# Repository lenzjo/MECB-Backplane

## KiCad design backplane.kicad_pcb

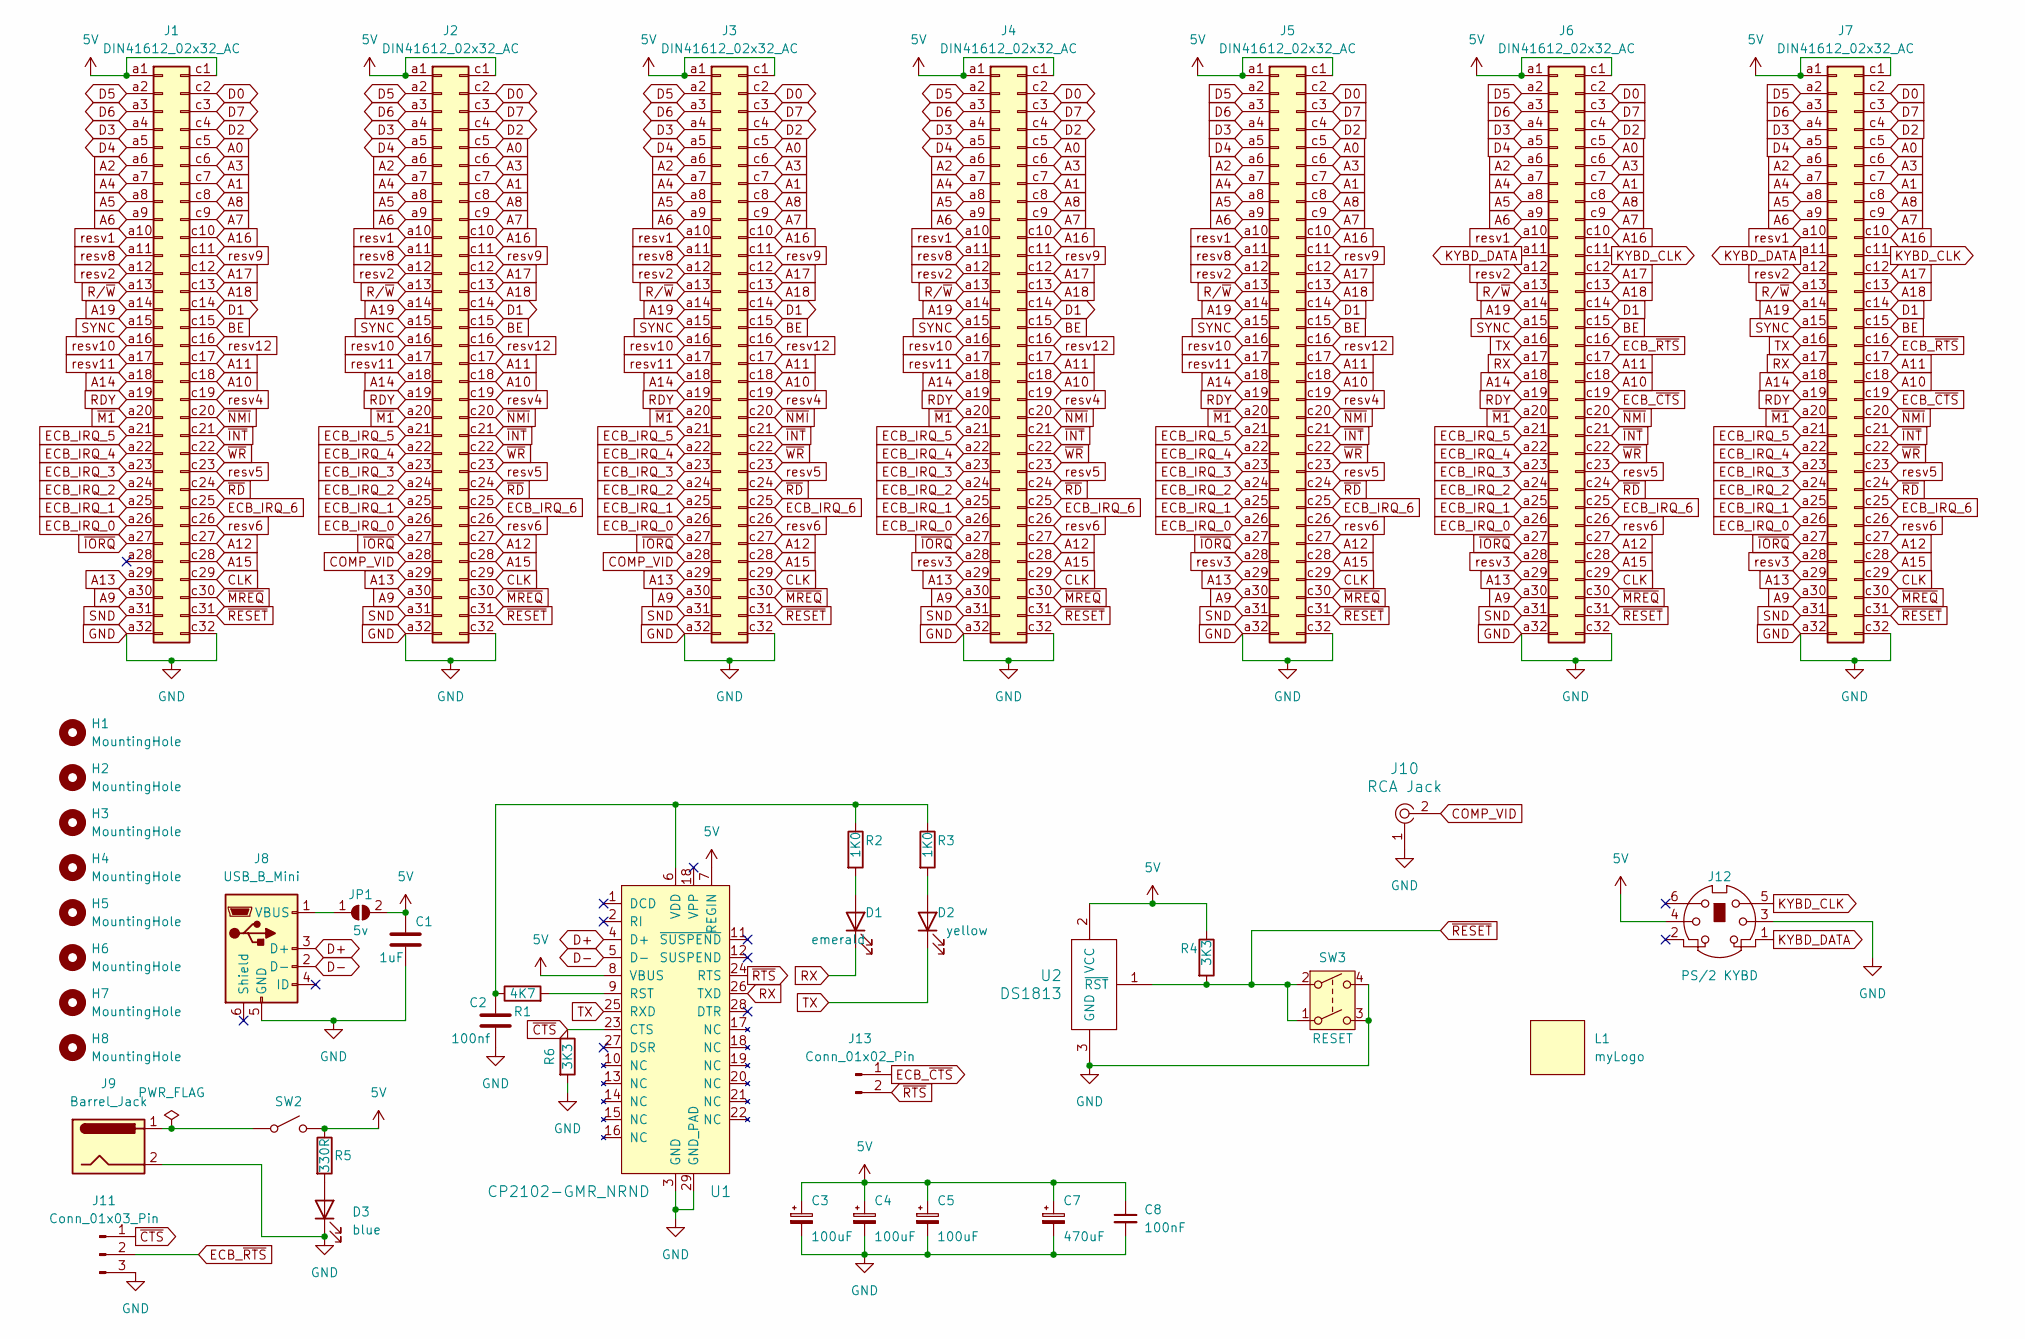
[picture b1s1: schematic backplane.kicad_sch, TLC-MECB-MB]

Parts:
C1: 1uF; C_0805_2012Metric; LCSC Part Number C28323
C2: 100nf; C_0805_2012Metric; LCSC Part Number C49678
C3, C4, C5: 100uF; CP_Radial_D6.3mm_P2.50mm
C7: 470uF; CP_Radial_D6.3mm_P2.50mm
C8: 100nF; C_Disc_D5.0mm_W2.5mm_P5.00mm
D1: emerald; LED_0603_1608Metric; LCSC Part Number C131259
D2: yellow; LED_0603_1608Metric; LCSC Part Number C264446
D3: blue; LED_1206_3216Metric; LCSC Part Number C131214
H1, H2, H3, H4, H5, H6, H7, H8: MountingHole; MountingHole_3.2mm_M3_DIN965
J1: DIN41612_02x32_AC; DIN41612_R_2x32_Female_Horizontal_THT
J2, J3, J4, J5, J6, J7: DIN41612_02x32_AC; DIN41612_C_2x32_Female_Vertical_THT
J8: USB_B_Mini; USB_Mini-B_5Pin
J9: Barrel_Jack; BarrelJack_GCT_DCJ200-10-A_Horizontal
J10: RCA Jack; RCA Video Jack; MPN 5-1814832-1; Digi-Key_PN A97594-ND
J11: Conn_01x03_Pin; PinHeader_1x03_P2.54mm_Vertical
J12: PS/2 KYBD; MINI-DIN-6-FULL-SHIELD
J13: Conn_01x02_Pin; PinHeader_1x02_P2.54mm_Vertical
JP1: 5v; SolderJumper-2_P1.3mm_Open_RoundedPad1.0x1.5mm
L1: myLogo; LOGO_sm
R1: 4K7; R_0805_2012Metric; LCSC Part Number C17673
R2, R3: 1K0; R_0805_2012Metric; LCSC Part Number C17513
R4, R6: 3K3; R_0805_2012Metric; LCSC Part Number C3016695
R5: 330R; R_0402_1005Metric; LCSC Part Number C156103
SW2: PTH_RA_h7.5mm; SPST Switch Mini
SW3: RESET; 12x12-Tactile-Switch
U1: CP2102-GMR_NRND; QFN-28-1EP_5x5mm_P0.5mm_EP3.35x3.35mm; MPN CP2102-GMR; Digi-Key_PN 336-1160-1-ND
U2: DS1813; 21-0248A_MXM

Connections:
5V: C1.1, C3.1, C4.1, C5.1, C7.1, C8.1, J1.a1, J1.c1, J2.a1, J2.c1, J3.a1, J3.c1, J4.a1, J4.c1, J5.a1, J5.c1, J6.a1, J6.c1, J7.a1, J7.c1, J12.4, JP1.2 (B), R4.1, R5.1, SW2.2 (B), U1.7 (REGIN), U1.8 (VBUS), U2.2 (VCC)
A0: J1.c5, J2.c5, J3.c5, J4.c5, J5.c5, J6.c5, J7.c5
A1: J1.c7, J2.c7, J3.c7, J4.c7, J5.c7, J6.c7, J7.c7
A2: J1.a6, J2.a6, J3.a6, J4.a6, J5.a6, J6.a6, J7.a6
A3: J1.c6, J2.c6, J3.c6, J4.c6, J5.c6, J6.c6, J7.c6
A4: J1.a7, J2.a7, J3.a7, J4.a7, J5.a7, J6.a7, J7.a7
A5: J1.a8, J2.a8, J3.a8, J4.a8, J5.a8, J6.a8, J7.a8
A6: J1.a9, J2.a9, J3.a9, J4.a9, J5.a9, J6.a9, J7.a9
A7: J1.c9, J2.c9, J3.c9, J4.c9, J5.c9, J6.c9, J7.c9
A8: J1.c8, J2.c8, J3.c8, J4.c8, J5.c8, J6.c8, J7.c8
A9: J1.a30, J2.a30, J3.a30, J4.a30, J5.a30, J6.a30, J7.a30
A10: J1.c18, J2.c18, J3.c18, J4.c18, J5.c18, J6.c18, J7.c18
A11: J1.c17, J2.c17, J3.c17, J4.c17, J5.c17, J6.c17, J7.c17
A12: J1.c27, J2.c27, J3.c27, J4.c27, J5.c27, J6.c27, J7.c27
A13: J1.a29, J2.a29, J3.a29, J4.a29, J5.a29, J6.a29, J7.a29
A14: J1.a18, J2.a18, J3.a18, J4.a18, J5.a18, J6.a18, J7.a18
A15: J1.c28, J2.c28, J3.c28, J4.c28, J5.c28, J6.c28, J7.c28
A16: J1.c10, J2.c10, J3.c10, J4.c10, J5.c10, J6.c10, J7.c10
A17: J1.c12, J2.c12, J3.c12, J4.c12, J5.c12, J6.c12, J7.c12
A18: J1.c13, J2.c13, J3.c13, J4.c13, J5.c13, J6.c13, J7.c13
A19: J1.a14, J2.a14, J3.a14, J4.a14, J5.a14, J6.a14, J7.a14
BE: J1.c15, J2.c15, J3.c15, J4.c15, J5.c15, J6.c15, J7.c15
CLK: J1.c29, J2.c29, J3.c29, J4.c29, J5.c29, J6.c29, J7.c29
COMP_VID: J2.a28, J3.a28, J10.2
D0: J1.c2, J2.c2, J3.c2, J4.c2, J5.c2, J6.c2, J7.c2
D1: J1.c14, J2.c14, J3.c14, J4.c14, J5.c14, J6.c14, J7.c14
D2: J1.c4, J2.c4, J3.c4, J4.c4, J5.c4, J6.c4, J7.c4
D3: J1.a4, J2.a4, J3.a4, J4.a4, J5.a4, J6.a4, J7.a4
D4: J1.a5, J2.a5, J3.a5, J4.a5, J5.a5, J6.a5, J7.a5
D5: J1.a2, J2.a2, J3.a2, J4.a2, J5.a2, J6.a2, J7.a2
D6: J1.a3, J2.a3, J3.a3, J4.a3, J5.a3, J6.a3, J7.a3
D7: J1.c3, J2.c3, J3.c3, J4.c3, J5.c3, J6.c3, J7.c3
D+: J8.3 (D+), U1.4 (D+)
D-: J8.2 (D-), U1.5 (D-)
ECB_IRQ_0: J1.a26, J2.a26, J3.a26, J4.a26, J5.a26, J6.a26, J7.a26
ECB_IRQ_1: J1.a25, J2.a25, J3.a25, J4.a25, J5.a25, J6.a25, J7.a25
ECB_IRQ_2: J1.a24, J2.a24, J3.a24, J4.a24, J5.a24, J6.a24, J7.a24
ECB_IRQ_3: J1.a23, J2.a23, J3.a23, J4.a23, J5.a23, J6.a23, J7.a23
ECB_IRQ_4: J1.a22, J2.a22, J3.a22, J4.a22, J5.a22, J6.a22, J7.a22
ECB_IRQ_5: J1.a21, J2.a21, J3.a21, J4.a21, J5.a21, J6.a21, J7.a21
ECB_IRQ_6: J1.c25, J2.c25, J3.c25, J4.c25, J5.c25, J6.c25, J7.c25
ECB_~CTS: J6.c19, J7.c19, J13.1
ECB_~RTS: J6.c16, J7.c16, J11.2
GND: C1.2, C2.2, C3.2, C4.2, C5.2, C7.2, C8.2, D3.1 (K), J1.a32, J1.c32, J2.a32, J2.c32, J3.a32, J3.c32, J4.a32, J4.c32, J5.a32, J5.c32, J6.a32, J6.c32, J7.a32, J7.c32, J8.5 (GND), J9.2, J10.1, J11.3, J12.3, R6.2, SW3.3, SW3.4, U1.3 (GND), U1.29 (GND_PAD), U2.3 (GND)
KYBD_CLK: J6.c11, J7.c11, J12.5
KYBD_DATA: J6.a11, J7.a11, J12.1
unnamed: D1.2 (A), R2.2
unnamed: D2.2 (A), R3.2
unnamed: D3.2 (A), R5.2
unnamed: J8.1 (VBUS), JP1.1 (A)
unnamed: J9.1, SW2.1 (A)
unnamed: R1.2, U1.9 (RST)
unnamed: C2.1, R1.1, R2.1, R3.1, U1.6 (VDD)
RDY: J1.a19, J2.a19, J3.a19, J4.a19, J5.a19, J6.a19, J7.a19
RX: D1.1 (K), J6.a17, J7.a17, U1.26 (TXD)
R/~W: J1.a13, J2.a13, J3.a13, J4.a13, J5.a13, J6.a13, J7.a13
SYNC: J1.a15, J2.a15, J3.a15, J4.a15, J5.a15, J6.a15, J7.a15
TX: D2.1 (K), J6.a16, J7.a16, U1.25 (RXD)
resv1: J1.a10, J2.a10, J3.a10, J4.a10, J5.a10, J6.a10, J7.a10
resv2: J1.a12, J2.a12, J3.a12, J4.a12, J5.a12, J6.a12, J7.a12
resv3: J4.a28, J5.a28, J6.a28, J7.a28
resv4: J1.c19, J2.c19, J3.c19, J4.c19, J5.c19
resv5: J1.c23, J2.c23, J3.c23, J4.c23, J5.c23, J6.c23, J7.c23
resv6: J1.c26, J2.c26, J3.c26, J4.c26, J5.c26, J6.c26, J7.c26
resv7: J1.a31, J2.a31, J3.a31, J4.a31, J5.a31, J6.a31, J7.a31
resv8: J1.a11, J2.a11, J3.a11, J4.a11, J5.a11
resv9: J1.c11, J2.c11, J3.c11, J4.c11, J5.c11
resv10: J1.a16, J2.a16, J3.a16, J4.a16, J5.a16
resv11: J1.a17, J2.a17, J3.a17, J4.a17, J5.a17
resv12: J1.c16, J2.c16, J3.c16, J4.c16, J5.c16
~CTS: J11.1, R6.1, U1.23 (CTS)
~INT: J1.c21, J2.c21, J3.c21, J4.c21, J5.c21, J6.c21, J7.c21
~IORQ: J1.a27, J2.a27, J3.a27, J4.a27, J5.a27, J6.a27, J7.a27
~M1: J1.a20, J2.a20, J3.a20, J4.a20, J5.a20, J6.a20, J7.a20
~MREQ: J1.c30, J2.c30, J3.c30, J4.c30, J5.c30, J6.c30, J7.c30
~NMI: J1.c20, J2.c20, J3.c20, J4.c20, J5.c20, J6.c20, J7.c20
~RD: J1.c24, J2.c24, J3.c24, J4.c24, J5.c24, J6.c24, J7.c24
~RESET: J1.c31, J2.c31, J3.c31, J4.c31, J5.c31, J6.c31, J7.c31, R4.2, SW3.1, SW3.2, U2.1 (~RST)
~RTS: J13.2, U1.24 (RTS)
~WR: J1.c22, J2.c22, J3.c22, J4.c22, J5.c22, J6.c22, J7.c22

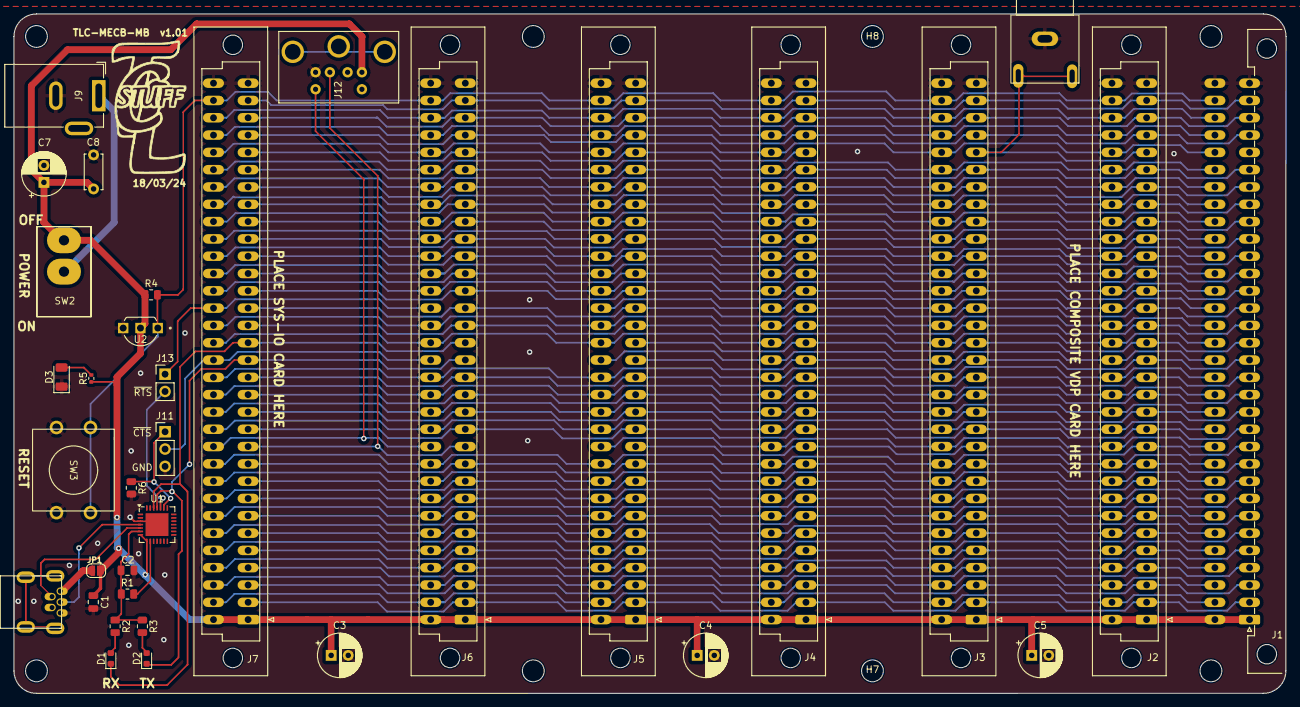
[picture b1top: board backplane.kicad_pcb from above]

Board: 2 copper layers, 186.7 x 99.7 mm, 43 parts (0 on the bottom side), 80 nets.
